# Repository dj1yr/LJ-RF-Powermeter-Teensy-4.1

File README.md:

Here is a collection of files for the RF Powermeter with Teensy 4.0/4.1.
Since I could not find any source files for the PCB, I designed two boards based on Robert Entwistle (WA2T) and the really impressive software by Johan G. Holstein (PD0LEW).
The Rev3n is based on a main board on which different RF boards can be plugged to find the best solution for each application.

I try to create a complete folder with all files here, my board files are welcome to be used and improved.

The board was designed with Kicad and the enclosure parts are designed with Inventor.

73' René

**Revisions:**

REV3.6:

-Connection J2 pin14 to 3.3V(L13 + C3 must be populated for the new 7" display) 

-LAN and User I/O Header removed
-SMA connection added to User IO 6 if frequency measurement is added

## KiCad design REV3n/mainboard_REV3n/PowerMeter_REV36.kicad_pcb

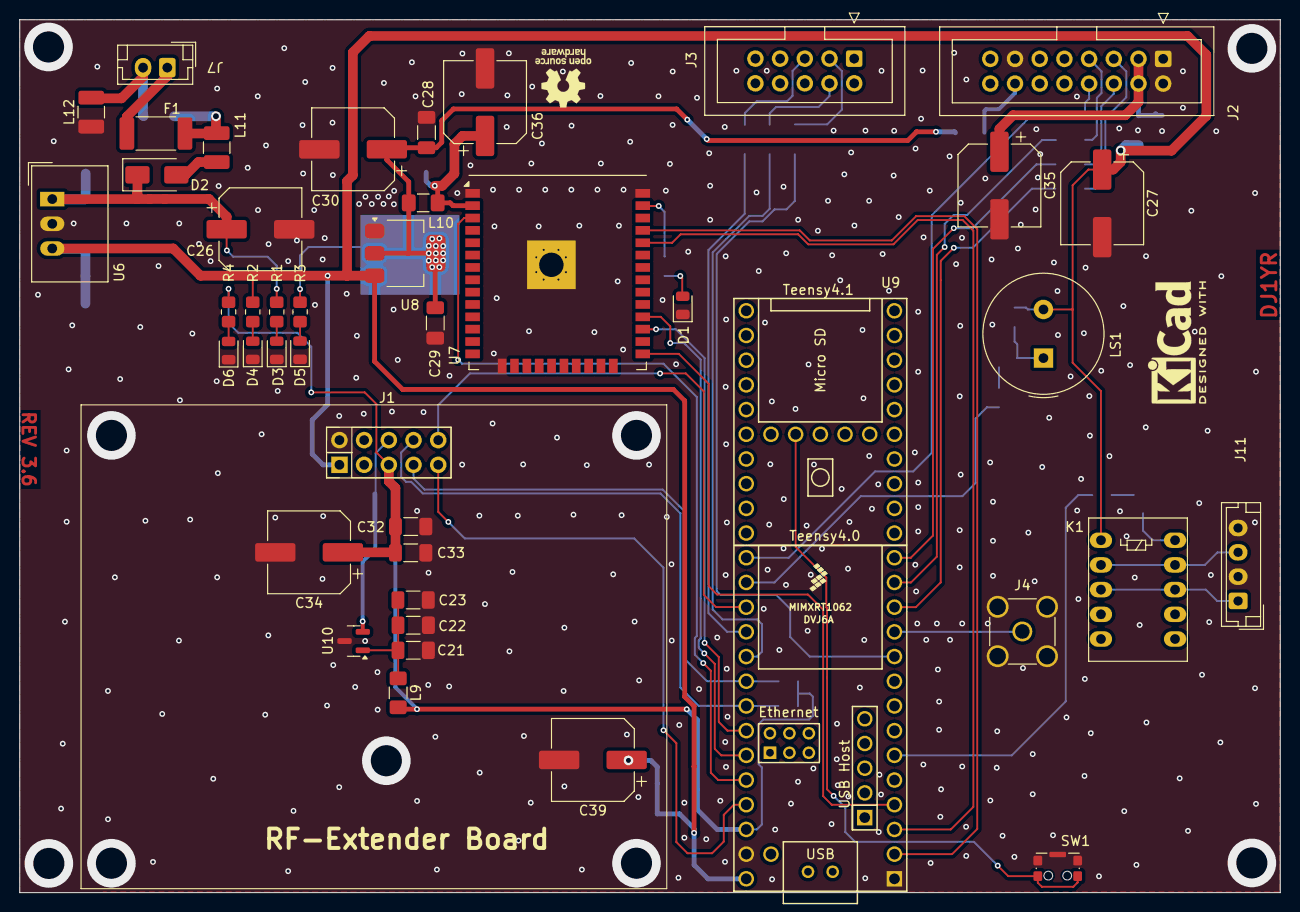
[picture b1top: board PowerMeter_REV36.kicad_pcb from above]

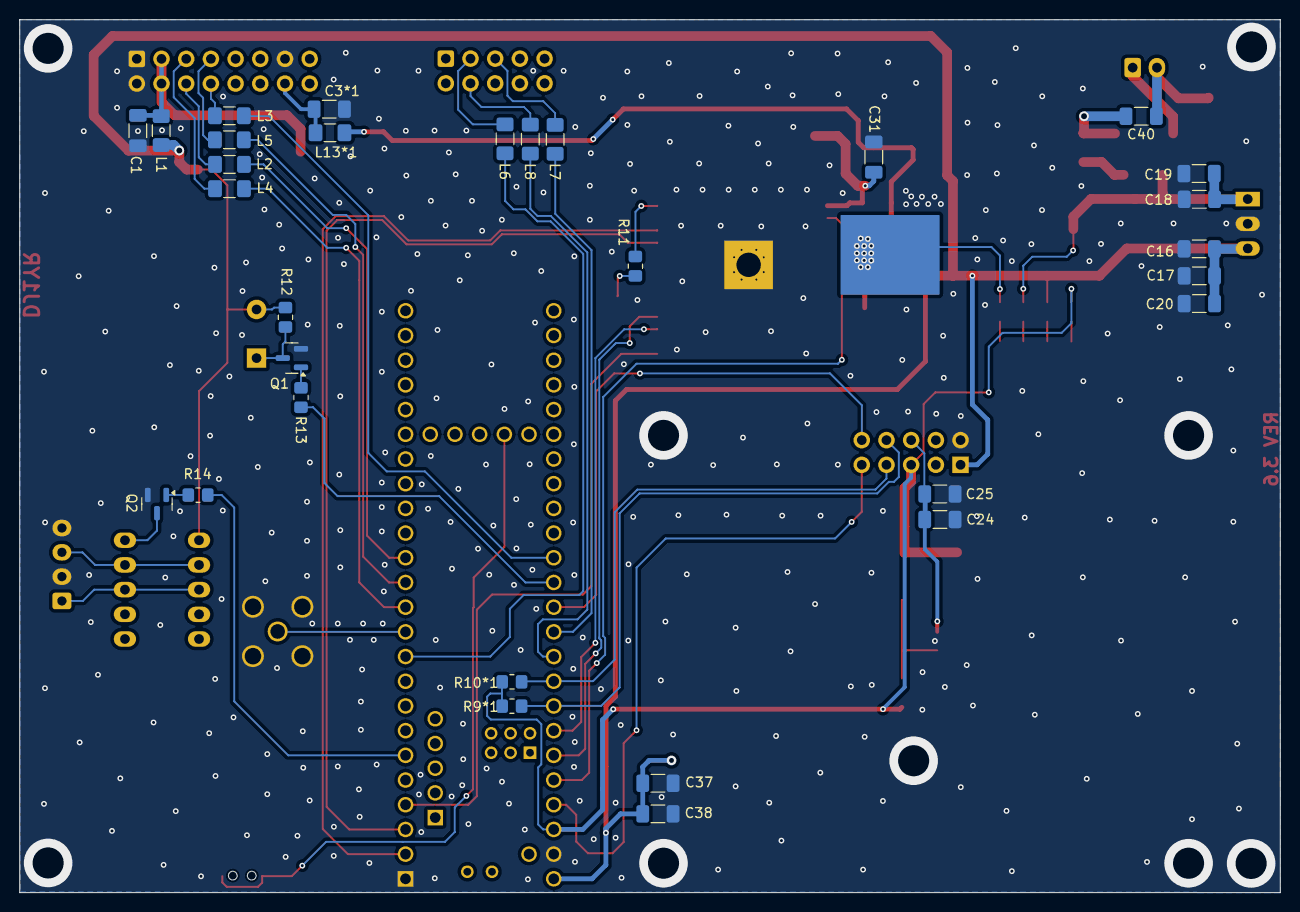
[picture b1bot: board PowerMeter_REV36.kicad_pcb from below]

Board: 2 copper layers, 129.6 x 89.8 mm, 73 parts (30 on the bottom side), 51 nets.

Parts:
C1, C3*1: 100n; C_1206_3216Metric_Pad1.33x1.80mm_HandSolder
C16, C19, C23, C25, C29, C33, C38: 1n; C_1206_3216Metric_Pad1.33x1.80mm_HandSolder
C17, C18, C22, C24, C28, C31, C32, C37, C40: 10n; C_1206_3216Metric_Pad1.33x1.80mm_HandSolder
C20, C21: 10µF; C_1206_3216Metric_Pad1.33x1.80mm_HandSolder
C26, C27, C30, C35, C36, C39: 100uF; CP_Elec_8x11.9
C34: 10uF; CP_Elec_8x11.9
D1: Wifi_EN; LED_0805_2012Metric
D2: US2BA; D_SMA
D3: +12V; LED_0805_2012Metric
D4: +5V; LED_0805_2012Metric
D5: 3V3_ESP; LED_0805_2012Metric
D6: +3V3; LED_0805_2012Metric
F1: Polyfuse; Fuse_2512_6332Metric_Pad1.52x3.35mm_HandSolder
J1: Extender Board; PinHeader_2x05_P2.54mm_Vertical
J2: Conn_02x08_Odd_Even; IDC-Header_2x08_P2.54mm_Vertical
J3: Conn_02x05_Odd_Even; IDC-Header_2x05_P2.54mm_Vertical
J4: Conn_Coaxial; SMA_Amphenol_132134-11_Vertical
J7: POWER CON; JST_EH_B2B-EH-A_1x02_P2.50mm_Vertical
J11: PTT IN/OUT; JST_EH_B4B-EH-A_1x04_P2.50mm_Vertical
K1: FRT5; Relay_DPDT_FRT5
L1, L9, L10: 4u7; L_1206_3216Metric_Pad1.42x1.75mm_HandSolder
L2, L3, L4, L5, L6, L7, L8, L13*1: 220n; L_1206_3216Metric_Pad1.42x1.75mm_HandSolder
L11, L12: L_Ferrite; L_1210_3225Metric_Pad1.42x2.65mm_HandSolder
LS1: Speaker_Crystal; Buzzer_TDK_PS1240P02BT_D12.2mm_H6.5mm
Q1, Q2: MMBT3904; SOT-23
R1, R9*1, R10*1: 2k2; R_0805_2012Metric_Pad1.20x1.40mm_HandSolder
R2, R3, R4, R11, R12: 1k; R_0805_2012Metric_Pad1.20x1.40mm_HandSolder
R13: 10k; R_0805_2012Metric_Pad1.20x1.40mm_HandSolder
R14: 4k7; R_0805_2012Metric_Pad1.20x1.40mm_HandSolder
SW1: CK_KMS2xxGP; SW_SPST_CK_KMS2xxGP
U6: TSR_1-24150; Converter_DCDC_TRACO_TSR-1_THT
U7: ESP32-WROOM-32U; ESP32-WROOM-32
U8: AMS1117-3.3; SOT-223-3_TabPin2
U9: Teensy4.1; Teensy41
U10: ISL60002DIH326Z; SOT-23

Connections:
2,6V REF: C24.2, C25.2, J1.6, U10.2 (Vout)
3.3V_Display_14: C28.2, C29.2, C30.1, L10.2, L13*1.2, R3.2, U8.2 (VO)
+3.3V: C32.2, C33.2, C34.1, J1.5, L9.2, R4.2, R9*1.1, R10*1.1, U9.46 (3V3)
+5V: C16.2, C17.2, C20.2, C27.1, C37.2, C38.2, C39.1, J1.1, K1.1, L1.2, LS1.2, R2.2, R12.2, U6.3 (Vout), U8.3 (VI), U9.48 (VIN)
+12V: C18.2, C19.2, C26.1, D2.1 (K), R1.2, U6.1 (Vin)
ESP_EN: U7.3 (EN), U9.44 (22_A8_CTX1)
ESP_RXD1: U7.35 (TXD0/IO1), U9.2 (0_RX1_CRX2_CS1)
ESP_RXD5: U7.27 (IO16), U9.42 (20_A6_TX5_LRCLK1)
ESP_TXD1: U7.34 (RXD0/IO3), U9.3 (1_TX1_CTX2_MISO1)
ESP_TXD5: U7.28 (IO17), U9.43 (21_A7_RX5_BCLK1)
GNDD: C1.1, C3*1.1, C16.1, C17.1, C18.1, C19.1, C20.1, C21.1, C22.1, C23.1, C24.1, C25.1, C26.2, C27.2, C28.1, C29.1, C30.2, C31.1, C32.1, C33.1, C34.2, C35.2, C36.2, C37.1, C38.1, C39.2, D1.1 (K), D3.1 (K), D4.1 (K), D5.1 (K), D6.1 (K), J1.2, J2.1, J2.2, J2.13, J4.2 (Ext), J11.2, J11.4, L12.1, Q1.2 (E), Q2.2 (E), SW1.1, SW1.SH (B), U6.2 (GND), U7.1 (GND), U7.15 (GND), U7.38 (GND), U7.39 (GND), U8.1 (GND), U9.1 (GND), U9.47 (GND), U10.3 (GND)
INP_SEL: J1.10, U9.37 (15_A1_RX3_SPDIF_IN)
INP_SEL2: J1.9, U9.45 (23_A9_CRX1_MCLK1)
IO0: U7.25 (IO0), U9.4 (2_OUT2)
unnamed: C40.2, F1.2, L11.2
unnamed: D1.2 (A), R11.1
unnamed: D2.2 (A), L11.1
unnamed: D3.2 (A), R1.1
unnamed: D4.2 (A), R2.1
unnamed: D5.2 (A), R3.1
unnamed: D6.2 (A), R4.1
unnamed: C1.2, C35.1, J2.3, J2.4, L1.1
unnamed: J2.5, L4.1
unnamed: J2.6, L2.1
unnamed: J2.7, L5.1
unnamed: J2.8, L3.1
unnamed: C3*1.2, J2.14, L13*1.1
unnamed: F1.1, J7.1
unnamed: C40.1, J7.2, L12.2
unnamed: J11.1, K1.3, K1.8
unnamed: J11.3, K1.2, K1.9
unnamed: Q1.1 (B), R13.2
unnamed: LS1.1, Q1.3 (C), R12.1
unnamed: Q2.1 (B), R14.2
unnamed: K1.10, Q2.3 (C)
unnamed: R11.2, U7.37 (IO23)
unnamed: C31.2, C36.1, L10.1, U7.2 (VDD)
unnamed: SW1.2, U9.53 (PROGRAM)
unnamed: C21.2, C22.2, C23.2, L9.1, U10.1 (Vin)
Piezo Alarm: R13.1, U9.36 (14_A0_TX3_SPDIF_OUT)
RA8875-5: L4.2, U9.12 (10_CS_MQSR)
RA8875-6: L2.2, U9.14 (12_MISO_MQSL)
RA8875-7: L5.2, U9.13 (11_MOSI_CTX1)
RA8875-8: L3.2, U9.35 (13_SCK_LED)
RA8875-33: L6.2, U9.10 (8_TX2_IN1)
RA8875-34: L8.2, U9.39 (17_A3_TX4_SDA1)
RA8875-35: L7.2, U9.38 (16_A2_RX4_SCL1)
SCL0: J1.8, R9*1.2, U9.41 (19_A5_SCL)
SDA0: J1.7, R10*1.2, U9.40 (18_A4_SDA)
SWR-Alarm: R14.1, U9.6 (4_BCLK2)
UI06: J4.1 (In), U9.11 (9_OUT1C)

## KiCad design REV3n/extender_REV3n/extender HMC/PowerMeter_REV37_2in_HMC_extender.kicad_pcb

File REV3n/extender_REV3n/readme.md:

I have designed another RF extender board with HMC849 as RF switch, first measurements looked very good. The plan is to design an RF board up to 23cm, which then has 3 coupler inputs. Some adjustments have to be made to the software, so for the time being a version with two coupler inputs and AD8307.
The question has been asked why I am not using PE4259 as in the original design.
It is very difficult to get original working PE4259, I had ordered many from ebay, Ali etc, all were fakes.
Then I found the test boards with HMC 349/849, you can easily test them and make sure they work.
Since I have a hot air soldering station, it was very easy to take these tested ICs and place them on my board.
I also tried soldering them on with a soldering iron, which also worked, and I added a 2mm VIA to the ground plane under the HMC.

-In the REV3.6 the 74HC04 was removed, this was only found in the REV3.5.
-Operating the HMC with 5V did not bring any significant improvement.

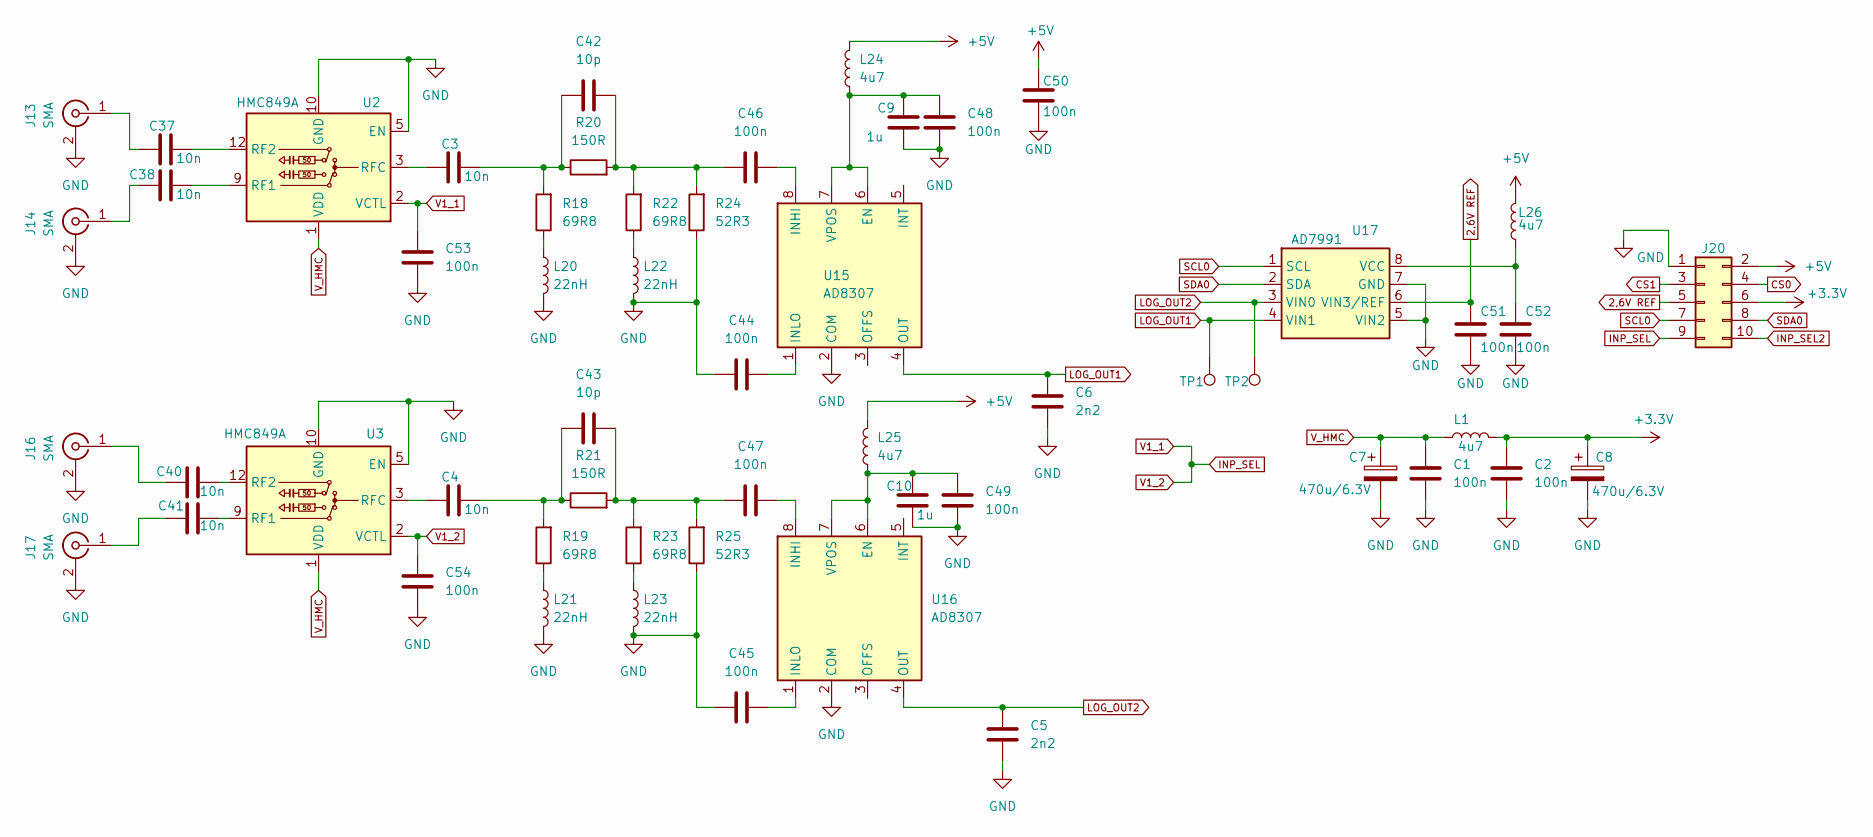
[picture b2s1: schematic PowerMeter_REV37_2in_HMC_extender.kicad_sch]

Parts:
C1, C2, C44, C45, C46, C47, C48, C49, C50, C51, C52, C53, C54: 100n; C_0805_2012Metric_Pad1.18x1.45mm_HandSolder
C3, C4, C37, C38, C40, C41: 10n; C_0805_2012Metric_Pad1.18x1.45mm_HandSolder
C5, C6: 2n2; C_0805_2012Metric_Pad1.18x1.45mm_HandSolder
C7, C8: 470u/6.3V; CP_Elec_6.3x5.4
C9, C10: 1u; C_0805_2012Metric_Pad1.18x1.45mm_HandSolder
C42, C43: 10p; C_0805_2012Metric_Pad1.18x1.45mm_HandSolder
J13, J14, J16, J17: SMA; SMA_BAT_Wireless_BWSMA-KWE-Z001
J20: Conn_02x05_Odd_Even; PinHeader_2x05_P2.54mm_Vertical
L1, L24, L25, L26: 4u7; L_1206_3216Metric_Pad1.42x1.75mm_HandSolder
L20, L21, L22, L23: 22nH; L_1206_3216Metric_Pad1.42x1.75mm_HandSolder
R18, R19, R22, R23: 69R8; R_1206_3216Metric_Pad1.30x1.75mm_HandSolder
R20, R21: 150R; R_1206_3216Metric_Pad1.30x1.75mm_HandSolder
R24, R25: 52R3; R_1206_3216Metric_Pad1.30x1.75mm_HandSolder
TP1, TP2: TestPoint; TestPoint_Pad_D1.0mm
U2, U3: HMC849A; LFCSP-16-1EP_4x4mm_P0.65mm_EP2.4x2.4mm
U15, U16: AD8307; SO-8_5.3x6.2mm_P1.27mm
U17: AD7991; TSOT-23-8

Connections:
2,6V REF: C51.2, J20.5, U17.6 (VIN3/REF)
+3.3V: C2.2, C8.1, J20.6, L1.1
+5V: C50.2, J20.2, L24.2, L25.2, L26.2
CS0: J20.4
CS1: J20.3
GND: C1.1, C2.1, C5.1, C6.1, C7.2, C8.2, C9.1, C10.1, C44.1, C45.1, C48.1, C49.1, C50.1, C51.1, C52.1, C53.1, C54.1, J13.2 (Ext), J14.2 (Ext), J16.2 (Ext), J17.2 (Ext), J20.1, L20.2, L21.2, L22.2, L23.2, R24.1, R25.1, U2.4 (GND), U2.5 (EN), U2.6 (GND), U2.7 (GND), U2.8 (GND), U2.10 (GND), U2.11 (GND), U2.13 (GND), U2.14 (GND), U2.15 (GND), U2.16 (GND), U2.17 (GND), U3.4 (GND), U3.5 (EN), U3.6 (GND), U3.7 (GND), U3.8 (GND), U3.10 (GND), U3.11 (GND), U3.13 (GND), U3.14 (GND), U3.15 (GND), U3.16 (GND), U3.17 (GND), U15.2 (COM), U16.2 (COM), U17.5 (VIN2), U17.7 (GND)
INP_SEL: C53.2, C54.2, J20.9, U2.2 (VCTL), U3.2 (VCTL)
INP_SEL2: J20.10
LOG_OUT1: C6.2, TP1.1, U15.4 (OUT), U17.4 (VIN1)
LOG_OUT2: C5.2, TP2.1, U16.4 (OUT), U17.3 (VIN0)
unnamed: C3.2, C42.1, R18.2, R20.1
unnamed: C4.2, C43.1, R19.2, R21.1
unnamed: C42.2, C46.1, R20.2, R22.2, R24.2
unnamed: C43.2, C47.1, R21.2, R23.2, R25.2
unnamed: C37.1, J13.1 (In)
unnamed: C38.1, J14.1 (In)
unnamed: C40.1, J16.1 (In)
unnamed: C41.1, J17.1 (In)
unnamed: L20.1, R18.1
unnamed: L21.1, R19.1
unnamed: L22.1, R22.1
unnamed: L23.1, R23.1
unnamed: C38.2, U2.9 (RF1)
unnamed: C37.2, U2.12 (RF2)
unnamed: C3.1, U2.3 (RFC)
unnamed: C41.2, U3.9 (RF1)
unnamed: C40.2, U3.12 (RF2)
unnamed: C4.1, U3.3 (RFC)
unnamed: C9.2, C48.2, L24.1, U15.6 (EN), U15.7 (VPOS)
unnamed: C46.2, U15.8 (INHI)
unnamed: C44.2, U15.1 (INLO)
unnamed: C10.2, C49.2, L25.1, U16.6 (EN), U16.7 (VPOS)
unnamed: C47.2, U16.8 (INHI)
unnamed: C45.2, U16.1 (INLO)
unnamed: C52.2, L26.1, U17.8 (VCC)
SCL0: J20.7, U17.1 (SCL)
SDA0: J20.8, U17.2 (SDA)
V_HMC: C1.2, C7.1, L1.2, U2.1 (VDD), U3.1 (VDD)

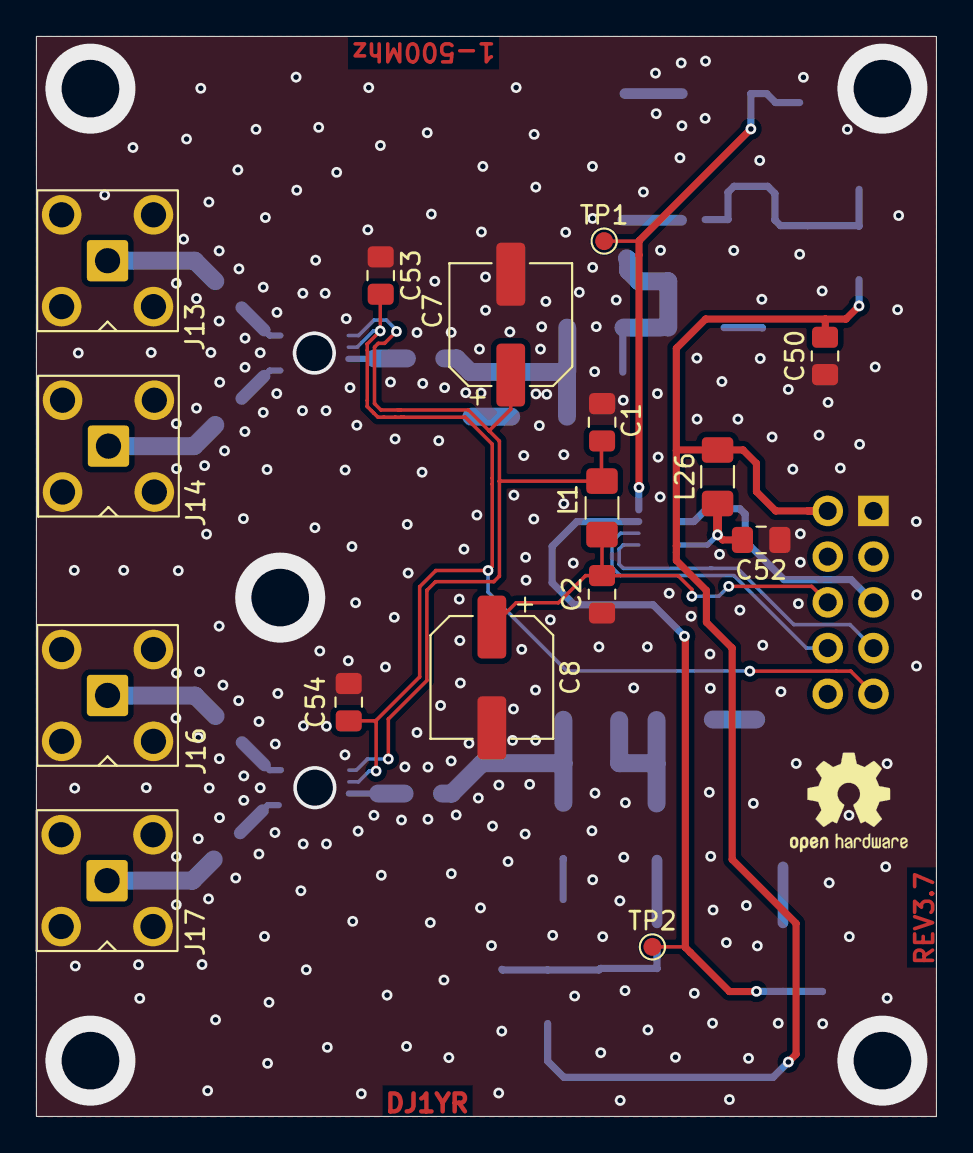
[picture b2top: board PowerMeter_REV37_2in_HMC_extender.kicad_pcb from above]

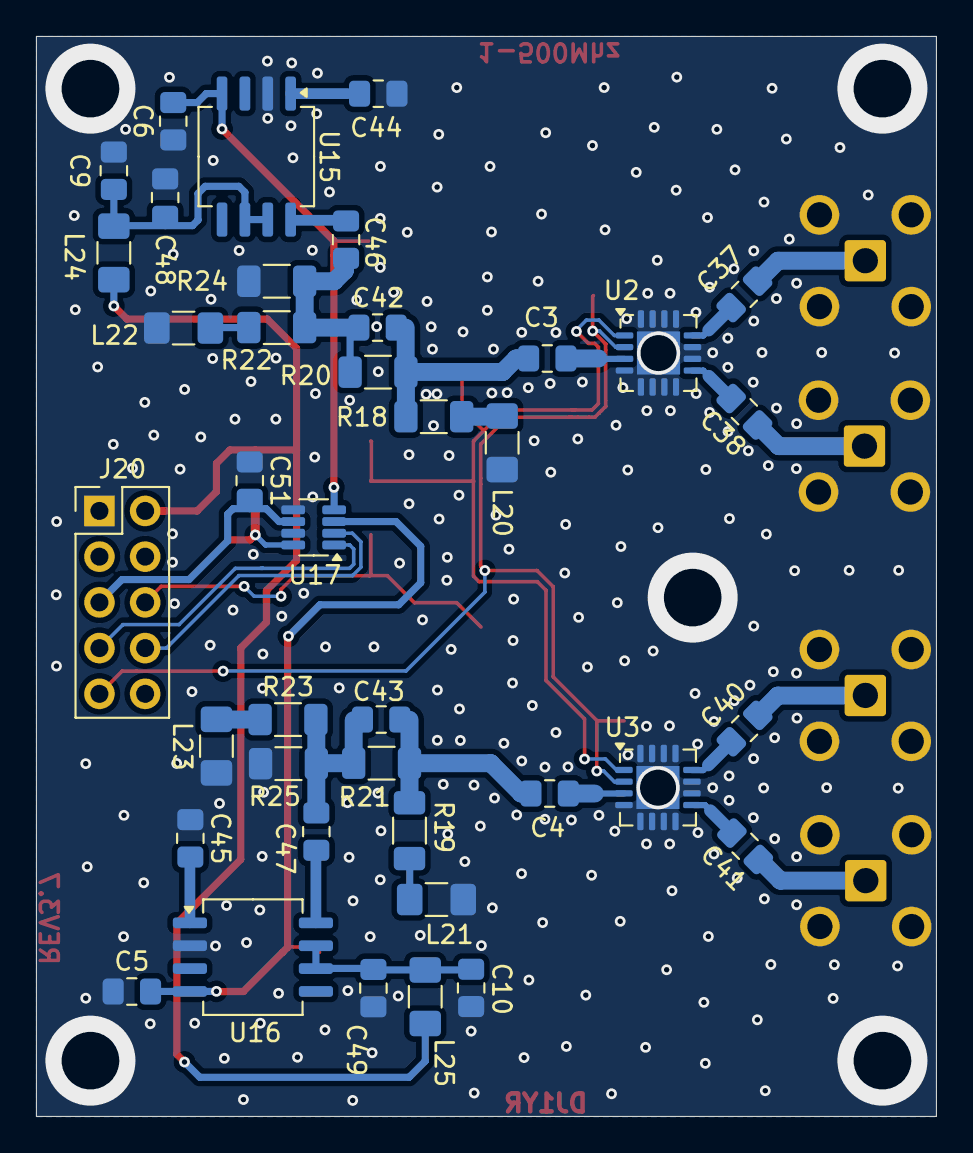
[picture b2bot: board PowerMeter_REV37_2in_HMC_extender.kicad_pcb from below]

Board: 2 copper layers, 50.0 x 60.0 mm, 55 parts (39 on the bottom side), 35 nets.

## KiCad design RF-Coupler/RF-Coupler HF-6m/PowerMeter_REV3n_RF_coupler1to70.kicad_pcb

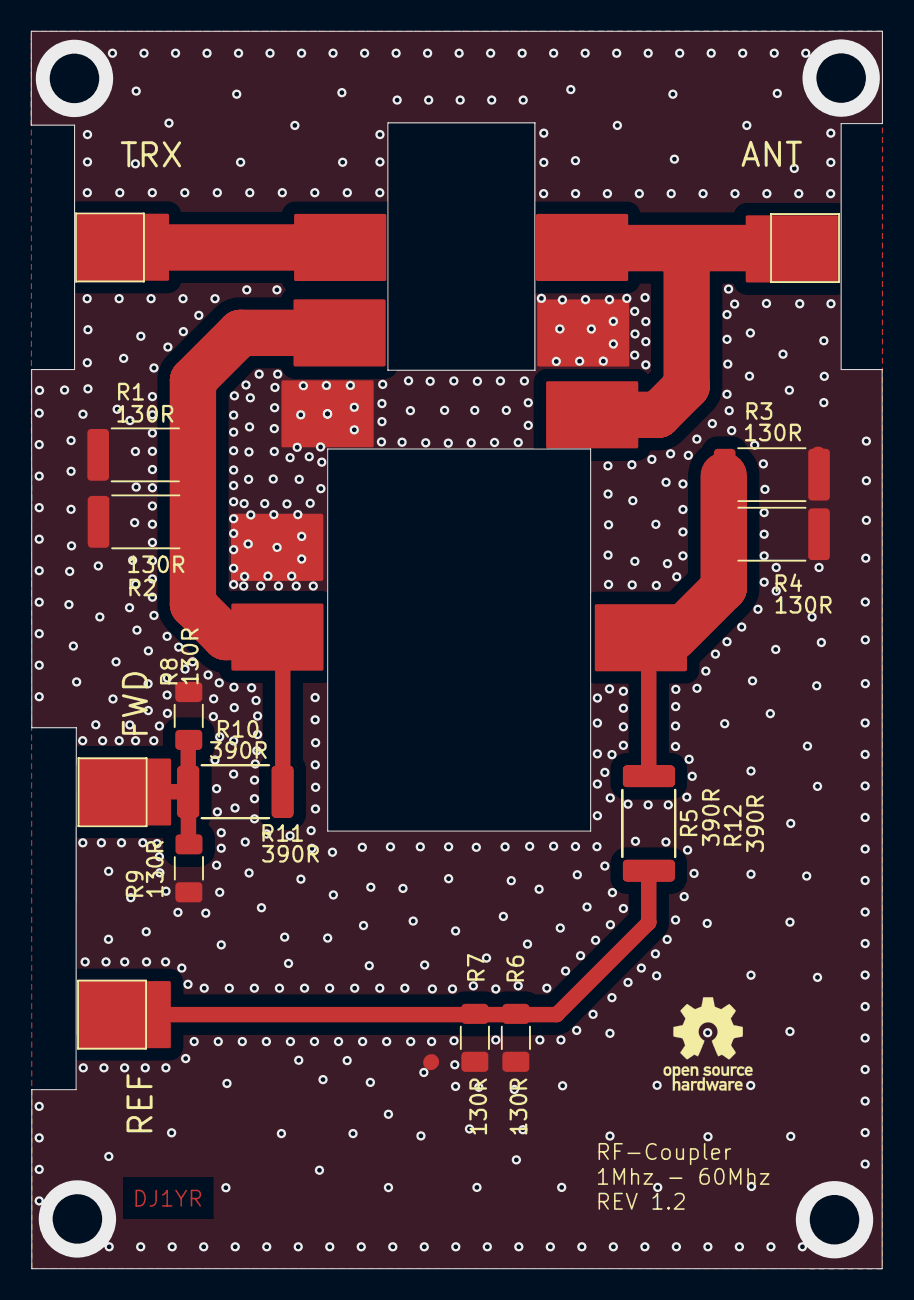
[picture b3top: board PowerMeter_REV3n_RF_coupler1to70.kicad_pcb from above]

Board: 2 copper layers, 55.0 x 80.0 mm, 16 parts (0 on the bottom side), 5 nets.

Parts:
ANT1: TestPoint_Pad_4.0x4.0mm
FWD1: TestPoint_Pad_4.0x4.0mm
R1, R2, R3, R4: 130R; R_2512_6332Metric_Pad1.40x3.35mm_HandSolder
R5, R10, R11, R12: 390R; R_2512_6332Metric_Pad1.40x3.35mm_HandSolder
R6, R7, R8, R9: 130R; R_1206_3216Metric_Pad1.30x1.75mm_HandSolder
REF1: TestPoint_Pad_4.0x4.0mm
TRX1: TestPoint_Pad_4.0x4.0mm

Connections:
GND: R1.2, R2.2, R3.2, R4.2, R6.2, R7.2, R8.2, R9.2
unnamed: FWD1.1, R8.1, R9.1, R10.1, R11.1
unnamed: R1.1, R2.1, R10.2, R11.2
unnamed: R3.1, R4.1, R5.1, R12.1
unnamed: R5.2, R6.1, R7.1, R12.2, REF1.1

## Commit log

2025-01-14 REV3n/
2025-01-14 Create REV3n
2025-01-14 Create REV27
2025-01-14 Create 123
2025-01-16 Create in work
2025-01-20 Add files via upload
    last changes from Johan (PD0LEW) - Beta!
    -add LAN on ESP32 with W5500
    -add USB-C connector, connected on Teensy
    -add extra display header (J4)*
    -add USER IO to ESP32
    -removed USER IO from teensy*
2025-02-03 Create place holder
2025-02-04 Create test
